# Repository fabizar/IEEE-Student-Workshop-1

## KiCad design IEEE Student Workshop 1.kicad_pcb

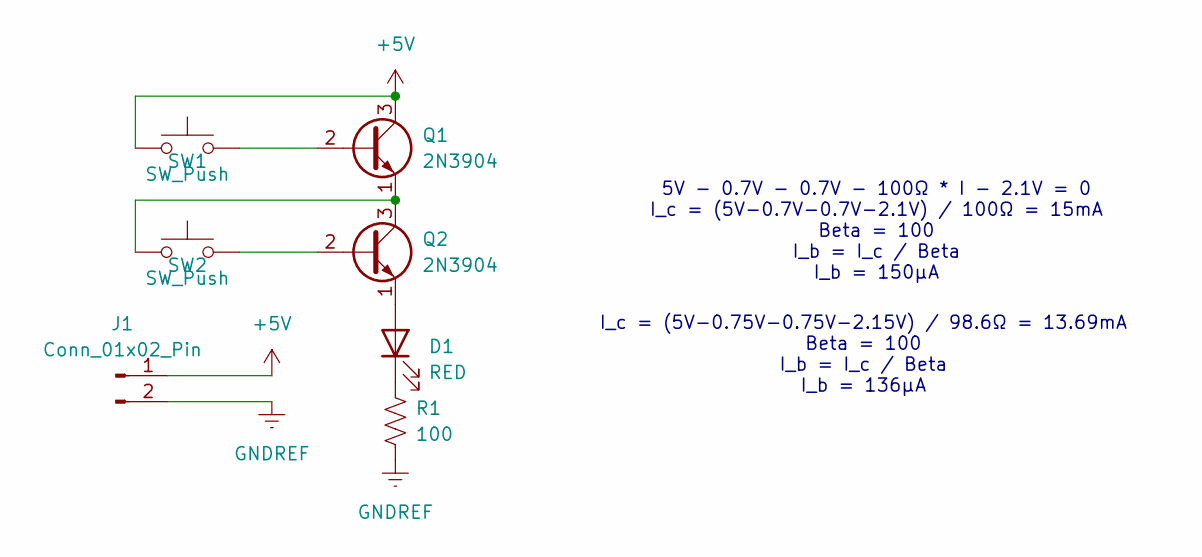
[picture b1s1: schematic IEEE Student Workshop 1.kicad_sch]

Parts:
D1: RED; LED_D5.0mm
J1: Conn_01x02_Pin; PinHeader_1x02_P2.54mm_Vertical
Q1, Q2: 2N3904; TO-92_Inline
R1: 100; R_Axial_DIN0207_L6.3mm_D2.5mm_P7.62mm_Horizontal
SW1, SW2: SW_Push; SW_PUSH_6mm

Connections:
+5V: J1.1, Q1.3 (C), SW1.1
GNDREF: J1.2, R1.1
unnamed: D1.2 (A), Q2.1 (E)
unnamed: D1.1 (K), R1.2
unnamed: Q1.2 (B), SW1.2
unnamed: Q1.1 (E), Q2.3 (C), SW2.1
unnamed: Q2.2 (B), SW2.2

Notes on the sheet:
I_c = (5V-0.75V-0.75V-2.15V) / 98.6Ω = 13.69mA Beta = 100 I_b = I_c / Beta I_b = 136µA
5V - 0.7V - 0.7V - 100Ω * I - 2.1V = 0 I_c = (5V-0.7V-0.7V-2.1V) / 100Ω = 15mA Beta = 100 I_b = I_c / Beta I_b = 150µA

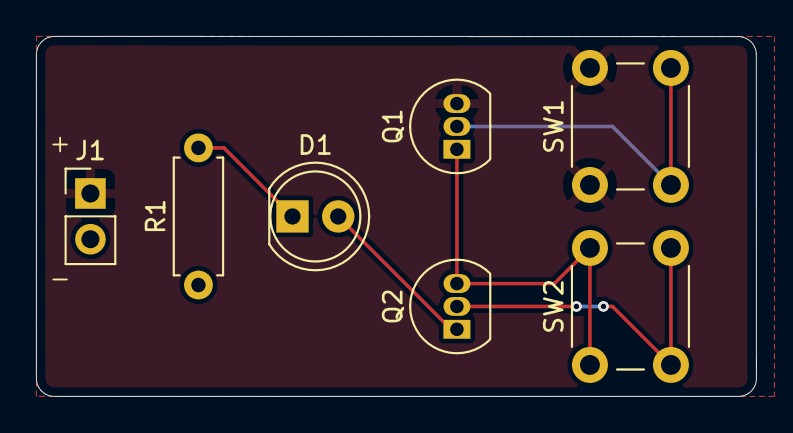
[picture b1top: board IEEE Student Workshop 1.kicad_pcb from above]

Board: 2 copper layers, 40.0 x 20.0 mm, 7 parts (0 on the bottom side), 7 nets.
